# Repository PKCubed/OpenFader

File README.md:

# OpenFader
### A project to modularize motorized faders with serial daisy chaining.

This board gets soldered onto the back of a motorized fader, and handles the control system aspect of the motorized faders. This board will handle PID control, with different modes and configuration options.
Each board has two UART connections (TX and RX). One UART connection is the upstream connection and connects to the previous fader or to the controller. The other UART connection is the downstream connection and connects to the following fader. When data flows from the controller to the first fader, the controller sends an integer fader address followed by data for that specific fader address. If this integer is not zero, the current fader modifies this address by subtracting 1, then sends the data on to the next fader. This process continuous until the address is zero. At this point, the receiving fader knows that the data is for itself, and it processes the data. Returning data from faders follows the same process but is reversed. Data requested from the fader comes after an address of zero. Each following fader in the path of the data increments this address on its way to the cotnroller. When this address and data gets to the controller, the address will have been incremented such that the controller knows exactly which fader sent this data.

For more protocol details, see the [PROTOCOL.md](PROTOCOL.md) file.

https://github.com/user-attachments/assets/ef170d1e-9a4b-43a3-9d26-493bcd82ac08

I've currently only designed a version for the Behringer MF60T and MF100T, which are some of the most economical motorized faders on the market. For other faders with different pin locations, the circuit is identical, but the locations of the pads will have to be redesigned. For testing, you can always use wires to attach the appropriate PCB pads to the fader.

---

This project is supported by [PCBWay](https://www.pcbway.com/)! I'd like to thank them for sponsoring this project and providing me free prototyping boards. The quality of my initial order is fantastic! They are a great option for PCB manufacturing and component assembly.

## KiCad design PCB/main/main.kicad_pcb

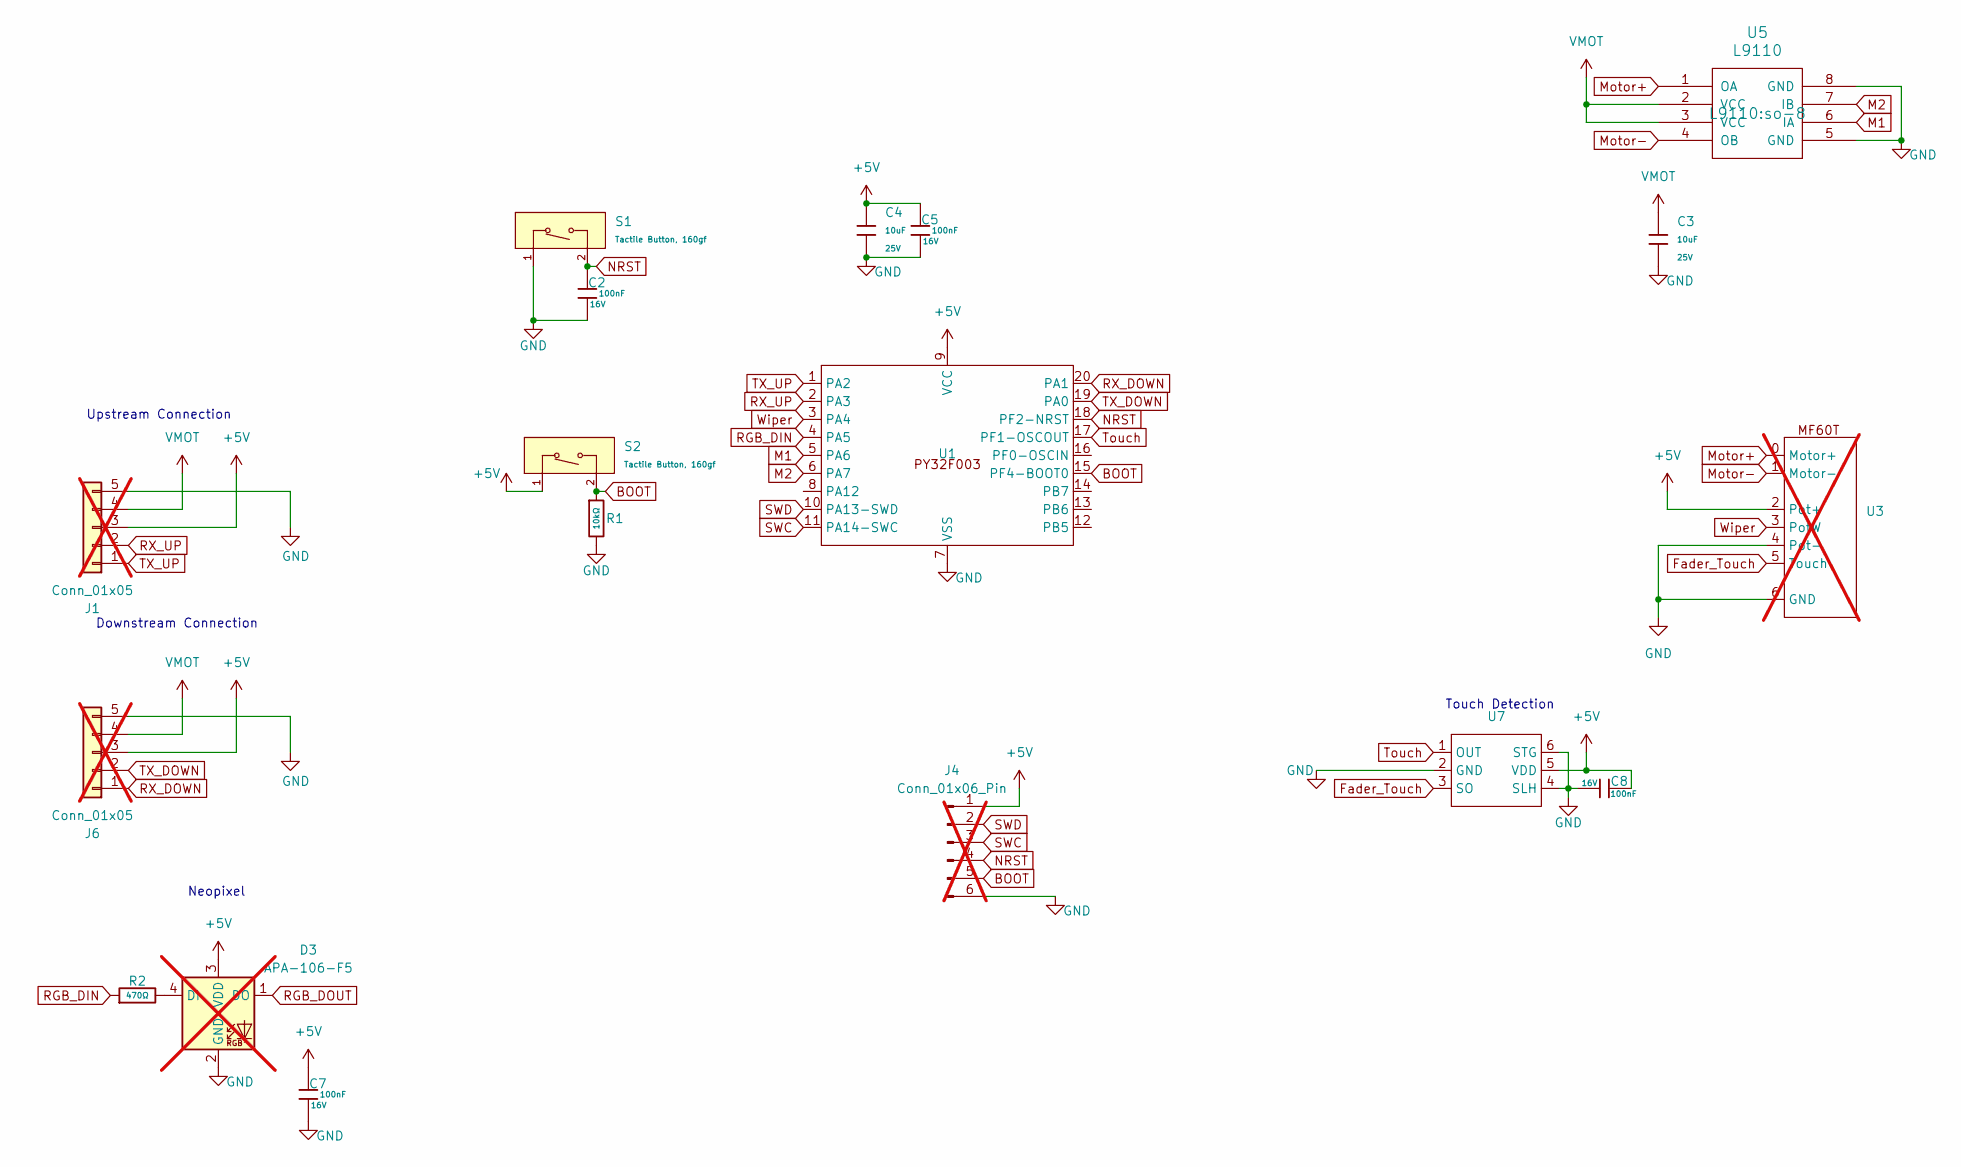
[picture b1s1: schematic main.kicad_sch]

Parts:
C2, C5, C7, C8: 100nF; C_0402; Voltage Rated 16V; Tolerance ±10%; Part CL05B104KO5NNNC; LCSC C1525
C3, C4: 10uF; C_0805; Voltage Rated 25V; Tolerance ±10%; Part CL21A106KAYNNNE; LCSC C15850
D3: APA-106-F5; LED_D5.0mm-4_RGB; not fitted
J1, J6: Conn_01x05; JST_XH_B5B-XH-AM_1x05_P2.50mm_Vertical; not fitted
J4: Conn_01x06_Pin; PinHeader_1x06_P2.54mm_Vertical; not fitted
R1: 10kΩ; R_0402; Overload Voltage (Max) 50V; Tolerance ±1%; Part 0402WGF1002TCE; LCSC C25744
R2: 470Ω; R_0402; Overload Voltage (Max) 50V; Tolerance ±1%; Part 0402WGF4700TCE; LCSC C25117
S1, S2: Tactile Button, 160gf; SW_TS-1088-AR02016; Voltage Rating (Dc) 12V; Part TS-1088-AR02016; LCSC C720477
U1: TSSOP-20_L6.5-W4.4-P0.65-LS6.4-BL; Part PY32F003F18P6TU; LCSC C5379864
U3: MF60T-MF100T; not fitted
U5: L9110; so-8; LCSC C513306
U7: SOT-23-6_L2.9-W1.6-P0.95-LS2.9-BL; Manufacturer Part TTP223-BA6-TD; LCSC Part Name 单键电容式触摸按键IC

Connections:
+5V: C4.1, C5.1, C7.1, C8.1, D3.3 (VDD), J1.3, J4.1, J6.3, S2.1 (A), U1.9 (VCC), U3.2 (Pot+), U7.5 (VDD)
BOOT: J4.5, R1.1, S2.2 (B), U1.15 (PF4-BOOT0)
Fader_Touch: U3.5 (Touch), U7.3 (SO)
GND: C2.2, C3.2, C4.2, C5.2, C7.2, C8.2, D3.2 (GND), J1.5, J4.6, J6.5, R1.2, S1.1 (A), U1.7 (VSS), U3.4 (Pot-), U3.6 (GND), U5.5 (GND), U5.8 (GND), U7.2 (GND), U7.4 (SLH), U7.6 (STG)
M1: U1.5 (PA6), U5.6 (IA)
M2: U1.6 (PA7), U5.7 (IB)
Motor+: U3.0 (Motor+), U5.1 (OA)
Motor-: U3.1 (Motor-), U5.4 (OB)
NRST: C2.1, J4.4, S1.2 (B), U1.18 (PF2-NRST)
unnamed: D3.4 (DI), R2.2
RGB_DIN: R2.1, U1.4 (PA5)
RGB_DOUT: D3.1 (DO)
RX_DOWN: J6.1, U1.20 (PA1)
RX_UP: J1.2, U1.2 (PA3)
SWC: J4.3, U1.11 (PA14-SWC)
SWD: J4.2, U1.10 (PA13-SWD)
TX_DOWN: J6.2, U1.19 (PA0)
TX_UP: J1.1, U1.1 (PA2)
Touch: U1.17 (PF1-OSCOUT), U7.1 (OUT)
VMOT: C3.1, J1.4, J6.4, U5.2 (VCC), U5.3 (VCC)
Wiper: U1.3 (PA4), U3.3 (PotW)

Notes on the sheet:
Neopixel
Upstream Connection
Touch Detection
Downstream Connection

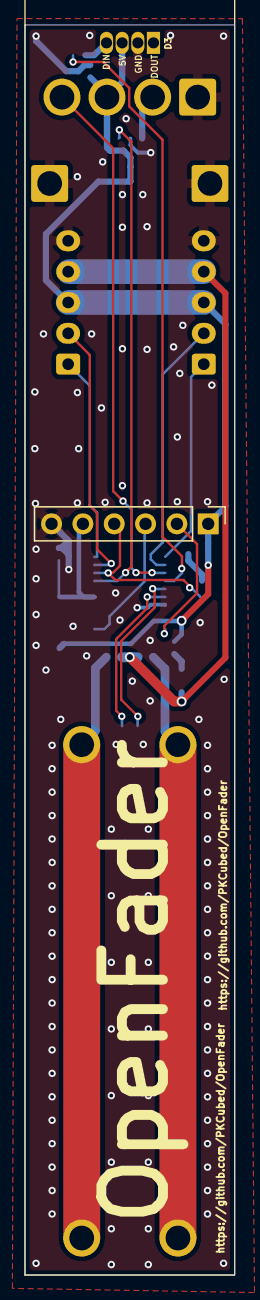
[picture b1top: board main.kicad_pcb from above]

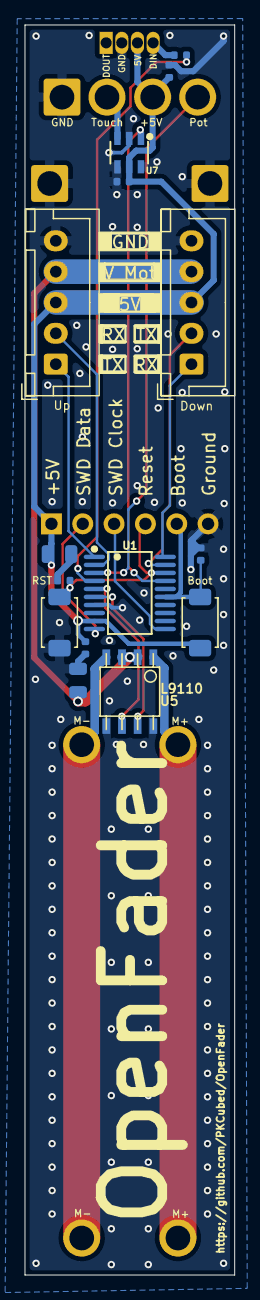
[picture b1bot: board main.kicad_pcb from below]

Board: 2 copper layers, 17.0 x 101.3 mm, 18 parts (15 on the bottom side), 20 nets.

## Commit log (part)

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2025-11-01 Initial dev test code
2025-11-02 Expand README with I2C Registers section
    Added detailed I2C register information for the OpenFader project.
2025-12-30 Added PCB Rev 1 Files
2025-12-30 Update README with a video
    Added a link to project assets in the README.
2025-12-30 Add image to README
    Added an image to the README file.
2025-12-30 Update README with Behringer MF60T details
    Clarified the design specifics for the Behringer MF60T fader and provided testing instructions.
2026-04-11 Initial commit on rp2040 version
    Switching to the cheaper, more capable RP2040 with an additional change from the I2C protocol to a daisy-chained serial protocol.
2026-04-12 Progress on new PCB schematic
2026-04-12 Progress on schematic
2026-05-08 Schematic Updates
2026-05-09 Started new branch
2026-05-09 PCB Nearly Complete
2026-05-09 PCB Updates
2026-05-11 Set components to DNP
2026-05-12 Progress on PCB
    Flipped side of board for components
2026-05-13 PCB Progress
2026-05-13 PCB Final Draft
2026-05-13 Generated Fab Files
2026-05-13 Revise README with project details and updates
    Updated project description and added details about UART connections and supported faders. Removed I2C register section and mentioned upcoming PCB development.
2026-05-13 Deleted old ATTiny1614 related files
2026-05-13 Update README to include protocol details reference
    Added a reference to the protocol details in the README.
2026-05-13 Correct link to protocol documentation in README
2026-05-13 Add image to PROTOCOL.md
2026-05-13 Update PROTOCOL.md with UART connection details
    Added description of UART connections for faders.
2026-05-13 Fix spelling and enhance UART protocol explanation
    Corrected spelling of 'incoming' and improved clarity of UART protocol description.
2026-05-13 Enhance PROTOCOL.md with hardware and UART details
    Added detailed sections on hardware, UART overview, daisy-chained structure, and data structure to PROTOCOL.md.
2026-05-13 Enhance PROTOCOL.md with timing statistics
    Added timing statistics for data transmission efficiency in OpenFader.
2026-06-12 Acknowledge PCBWay support in README
    Added acknowledgment for PCBWay's support and sponsorship.
2026-06-13 Added separator
